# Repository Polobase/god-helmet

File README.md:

# God Helmet: 8-coil weak-field headset (ESP32 + AD5328 + web app over Bluetooth or USB)

A DIY recreation of the Persinger/Koren "God Helmet", the 8-coil Shakti and the circumcerebral "Octopus":
- 8 small coils on a Velcro headband;
- an AD5328 8-channel ±10 V DAC;
- an ESP32 that runs the signals in real time: ESP32-S3, classic ESP32, ESP32-C3 or ESP32-C6, without a display;
- a **web app** (the Nuxt site in [site/](site)) that connects over **Bluetooth LE** or a **USB cable**, and installs the firmware;
- or, without phone or computer, a **2.8" touchscreen board** that runs the programs from its microSD card ([docs/STANDALONE.md](docs/STANDALONE.md)).

It ships **176 programs**, each checked against its source ([docs/PRESET_AUDIT.md](docs/PRESET_AUDIT.md)): Todd Murphy's Shiva and Shakti sessions rebuilt from the vendor's descriptions (with reversed-polarity coils where the Shakti wiring needs them), the Persinger lab's protocols (sensed presence, Thomas pulse, circumcerebral rotations, Swann remote viewing, paired sessions), the timing of clinical low-field methods (LFMS, T-PEMF, Cnp, theta-burst, BHFS), and the independent sham-controlled tests. Each program states the evidence for the original protocol and how closely this helmet can follow it: 14 play published values as published, 133 are rebuilt from descriptions, 16 copy only the timing of a method whose field is out of reach, and 13 are this project's own designs. Whether the first build can host the experiments at all is the subject of [docs/HARDWARE_AUDIT.md](docs/HARDWARE_AUDIT.md). Each program's page also has a **Brain** tab that shows where each program's field goes on a 3D brain, **30 guided sessions** with beat audio and questionnaires, and the means to **test it all honestly**:
- blinded real/sham sessions;
- hash-committed, blind-judged remote-viewing and telepathy trials with exact statistics.

> **Read [docs/SAFETY.md](docs/SAFETY.md) first.** Not for people with epilepsy or seizure history, psychiatric conditions, or implanted electronics. Battery power only. Experimental, non-medical.
>
> **Honest expectations.** The fields are about 1–8 µT at the cortex, about a million times weaker than TMS, and the induced electric field is microvolts to millivolts per metre. The best double-blind test (Granqvist 2005, N = 89) found no effect of the field; suggestibility predicted the experiences. See [docs/RESEARCH.md](docs/RESEARCH.md).

## How it fits together

```
 phone / laptop browser                     control box                                  headband
 ┌──────────────────────┐ Bluetooth / USB┌──────────────┐  SPI + LDAC  ┌──────────┐ 2.2 kΩ ×8  ┌─────────┐
 │ web app (site/):     │◄──────────────►│  ESP32       │─────────────►│ AD5328   │──────────► │ 8 coils │
 │ programs,            │  JSON-RPC +    │  2 kHz engine│              │ ±10 V ×8 │◄─ returns ─│         │
 │ placement, trials    │  live status   │  log, trials │  PhotoMOS ◄──┤          │  PhotoMOS  └─────────┘
 └──────────────────────┘                └──────────────┘  STOP button └──────────┘
```

- **The app** (tabs: Programs, Guides, Trials, Log, Helmet, Docs) holds:
  - the program library, searchable, browsed by category, by placement (all 47 placements in use), by scalp site (a site explorer for every 10-10 site) or by the experience a program aims at;
  - a page for each program with tabs:
    - **Overview:** phases, waveforms and an in-browser preview of the coil activity;
    - **Placement:** the coils on a head map from above and from both sides, and a coil-by-coil checklist with tape-measure directions in centimetres for your head;
    - **Brain:** estimated field per brain region (cored-coil model on the Brainnetome and CerebrA atlases), what electrode or TMS stimulation of each region produced, and the claims made for it;
    - **Sources:** the evidence level and the sources;
  - a Start panel on each program page that lists what is ready (connection, safety page, head measured, coils placed, calibration, time since the last session);
  - guided sessions (Gateway-style, remote viewing, ESP training, sleep) with binaural, monaural or isochronic audio, a blinded helmet arm and questionnaires;
  - blinded remote-viewing and telepathy trials with their picture pool (Trials), and calibration, the wiring check, settings and firmware install (Helmet);
  - all documentation (the Docs tab renders `docs/*.md` and a reference of every program).

  It has a **demo mode** that runs the same engine in the browser, so everything can be explored without hardware.
- **The helmet** holds:
  - the real-time engine, with all 8 coils updated together at 2 kHz;
  - the hidden blind choices (real/sham, RV target, with SHA-256 commitments);
  - the session and trial log;
  - the safety interlocks: STOP button, arming switch, field ceiling, 60-min cap.

  A running session continues if the phone or computer disconnects, and the app shows it again when it reconnects. If the helmet itself restarts, the session's log entry says why and how long it ran.

## What's here

| Path | Contents |
|---|---|
| [docs/RESEARCH.md](docs/RESEARCH.md) | The evidence review: Persinger lab, independent tests, Murphy's claims, mainstream low-field science, psi evidence, **states → brain regions → helmet protocols**, lecture notes |
| [docs/HISTORY.md](docs/HISTORY.md) | Military, intelligence and health-agency history: ELF research, remote-viewing programmes, Gateway, the replication controversy, WHO/IARC/ICNIRP |
| [docs/EFFECT_SENSED_PRESENCE.md](docs/EFFECT_SENSED_PRESENCE.md), [docs/EFFECT_OUT_OF_BODY.md](docs/EFFECT_OUT_OF_BODY.md), [docs/EFFECT_REMOTE_VIEWING.md](docs/EFFECT_REMOTE_VIEWING.md) | Articles on the three most reported effects: what people report, the lab record and independent tests, the science without a helmet, checked YouTube videos, reading lists and how to test each with this helmet |
| [docs/SIGNALS.md](docs/SIGNALS.md) | What the coils play: coil physics and ICNIRP compliance, the Persinger-lab signals rebuilt from primary sources, Murphy's signal families, clinical timings |
| [docs/PRESET_FORMAT.md](docs/PRESET_FORMAT.md) | The program file format, every signal and coil mode, the pulse-table generators, the preset checker |
| [docs/PRESET_AUDIT.md](docs/PRESET_AUDIT.md) | Every program against its source: flaw, decision, deciding page |
| [docs/HARDWARE_AUDIT.md](docs/HARDWARE_AUDIT.md) | Can the first build host the experiments? Verdict per family, ledger, bench protocol |
| [docs/HARDWARE_REQUIREMENTS.md](docs/HARDWARE_REQUIREMENTS.md) | The changes the audit forces, with numbers and cost |
| [docs/AUDIT_SUMMARY.md](docs/AUDIT_SUMMARY.md) | The audit on one page |
| docs/LIBRARY_*.md | Reading notes from the library, one page per family of sources: what each paper or vendor page states, with page and passage |
| [docs/BRAIN_VIEW.md](docs/BRAIN_VIEW.md) | How the brain view's field map is computed, its accuracy, data and licences |
| [docs/GUIDES.md](docs/GUIDES.md), [docs/QUESTIONNAIRES.md](docs/QUESTIONNAIRES.md) | Guided-session format, audio engine, questionnaires and scoring |
| [docs/WIRING.md](docs/WIRING.md) | Schematic, coil leads (inner = signal, outer = return), pin tables (S3, classic ESP32, C3, C6, 2.8" display board), arming switch, Cat6A pair mapping |
| [docs/STANDALONE.md](docs/STANDALONE.md) | The 2.8" touchscreen board without the app: flashing, the SD-card program pack, clock, screens |
| [docs/PLACEMENT.md](docs/PLACEMENT.md) | The 10-10 system, finding sites with a tape measure, the standard and program-specific layouts, depth and field per target |
| [docs/CALIBRATION.md](docs/CALIBRATION.md) | Bench test of the module, wiring checks, µT/mA calibration with a phone |
| [docs/EXPERIMENTS.md](docs/EXPERIMENTS.md) | Blinded sessions, remote-viewing and telepathy protocols, statistics |
| [docs/BLE_PROTOCOL.md](docs/BLE_PROTOCOL.md) | GATT service, framing, the USB line protocol, operations, session JSON, trial commitment |
| [docs/SAFETY.md](docs/SAFETY.md) | Contraindications, rules, built-in safeguards |
| [presets/](presets) | The 176 programs (JSON), shared by the app and the firmware tests. `presets/archive/` holds the 28 that were taken out |
| [guides/](guides) | The 30 guided sessions (JSON) |
| [firmware/](firmware) | PlatformIO project: engine, Bluetooth and USB transports, experiments, log |
| [site/](site) | The Nuxt site: landing page, articles, docs and the control app. `site/core/` holds the engine, protocol and library code that is tested against the firmware. Cloudflare Pages builds it; `.github/workflows/pages.yml` publishes the firmware images for its installer |
| [hardware/](hardware) | Bill of materials, coil clip (OpenSCAD), schematic generator |
| [tools/](tools) | Python: coil field estimate, point tables, WAV → table, calibration fit, trial statistics; Node: brain-view asset builder |

## Quick start

### Supported boards

| Board | Chip | Bluetooth | USB | Display | Firmware env |
|---|---|---|---|---|---|
| ESP32-S3-DevKitC-1 (N8R8 / N16R8, 8 MB flash) | ESP32-S3 | yes | yes | – | `esp32s3` |
| ESP32 DevKitC (WROOM-32, 4 MB) | ESP32 | yes | yes | – | `esp32dev` |
| ESP32-C3-DevKitM-1, C3 Super Mini (4 MB) | ESP32-C3 | yes | yes | – | `esp32c3` |
| ESP32-C6-DevKitC-1 and other C6 boards (4 MB or more) | ESP32-C6 | yes | yes | – | `esp32c6` |
| 2.8" ESP32-32E display board | ESP32 | optional | yes | touchscreen | `esp32e_lcd28` |

Pins for each board: [docs/WIRING.md](docs/WIRING.md).

**Install from the app** (no other software): Helmet → **Install the firmware**, in Chrome or Edge on a computer, with the board on USB. It recognises the chip and asks before erasing.

**Firmware** ([PlatformIO](https://platformio.org/)):

```sh
cd firmware
./test/run_host_tests.sh      # engine, JSON, BLE framing, every preset rendered at 2 kHz
pio run -e esp32s3 -t upload  # ESP32-S3-DevKitC-1 (-e esp32dev, -e esp32c3, -e esp32c6; -e esp32e_lcd28: 2.8" display board)
pio device monitor            # prints the Bluetooth name, e.g. GodHelmet-3F2A
scripts/web_bundle.sh ../site/public/firmware     # images + manifests for the app's installer (CI does this)
```

Standalone touchscreen board: `pio run -e esp32e_lcd28 -t upload`, then `npm run sd-pack -- <dir>` in `site/` for the SD card ([docs/STANDALONE.md](docs/STANDALONE.md)).

**App:**

```sh
cd site
npm install
npm test                      # JS engine matches the C++ engine; field model; guides; protocol and trial logic; every program file
npm run check-presets         # validate every program file (also one file: node scripts/check-preset.mjs ../presets/<id>.json)
npm run table -- list         # exact pulse tables (theta-burst, Thomas, LFMS, ...)
npm run dev                   # http://localhost:3000 (Web Bluetooth and Web Serial work on localhost)
```

**Deploy:** Cloudflare Pages builds `site/` on every push ([site/README.md](site/README.md)). The firmware images for the installer are built by `.github/workflows/pages.yml` and served from GitHub Pages (Settings → Pages → Source: **GitHub Actions**).

**First use:**
1. Open the app in Chrome/Edge (iPhone: Bluefy) and press **Bluetooth**, or plug the helmet into the computer and press **USB**.
2. Read and accept **Safety**.
3. Do the bench test and calibration (docs/CALIBRATION.md) before wearing the helmet.

## Status

- **Verified here:**
  - all five firmware targets build;
  - host unit tests pass;
  - the JavaScript engine reproduces the C++ engine's output for every preset (whole sessions plus a 3.5 ms-resolution window);
  - protocol, blind reveal and trial commitment logic are tested against the demo helmet;
  - the app builds and runs in a headless browser in demo mode.
- **Not yet verified on hardware:**
  - BLE with a real phone;
  - the module's transfer function;
  - SPI/LDAC timing;
  - the coils' real µT/mA.

  docs/CALIBRATION.md walks through them.

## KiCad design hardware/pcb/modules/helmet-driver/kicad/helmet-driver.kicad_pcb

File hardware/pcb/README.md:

# hardware/pcb: the helmet driver board as code

This folder holds the god-helmet's controller board, **helmet-driver** (`modules/helmet-driver/`: an ESP32-S3,
eight current-output coil drivers and two isolated tES outputs, fed from USB-C), and the toolchain that turns it
into order files for JLCPCB:

```
spec.md + module.yaml ─► schematic.ts ─► bun run sch ─► PDF review ─► sch:approve ─► bun run pcb ─► bun run fab ─► bun run order
                         (KiCad 10, ERC 0/0,           (you)         (sha256 in     (placed,        (Gerbers, BOM,   (ORDER.md and
                          netlist round-trip)                          module.yaml)   routed, DRC)    CPL, README)     upload files)
            ngspice benches (bun run sim) check the critical circuits along the way
```

The schematic is written as TypeScript (`modules/<id>/schematic.ts`) and generated into a native KiCad 10
schematic, one sheet or a root sheet with pages (`sheets`, [docs/schematic-as-code.md](docs/schematic-as-code.md)
§3a); parts come from `parts/*.yaml`, with their KiCad symbols and footprints vendored in `lib/kicad/`. The
toolchain builds standalone PCBs of this kind: one board per `modules/<id>/`, 2 or 4 copper layers, assembled by
JLCPCB.

## Prerequisites

- **Bun ≥ 1.4.2** (`bun install` once, for zod, yaml and fflate)
- **KiCad 10.0.x** (tested with 10.0.6): `kicad-cli` and KiCad's bundled Python with `pcbnew`
- **ngspice** (47 or newer) for `bun run sim`
- **Java ≥ 25** for the Freerouting autorouter (Homebrew's keg-only OpenJDK is found without PATH). Freerouting
  2.4.1 itself is fetched into `.tools/` on first use, sha256-pinned.
- TI SPICE models: `bun run models:fetch` downloads them into the gitignored `models/` (TI's terms: never committed).

`bun run doctor` checks all of these and prints install hints; it never installs anything. Details and known
KiCad issues: [docs/environment.md](docs/environment.md).

## Commands

Run from `hardware/pcb/`. `<id>` is a folder name in `modules/` (`helmet-driver`).

| Command | What it does |
|---|---|
| `bun run doctor` | report tools, versions and paths |
| `bun run validate [-- <id>]` | check `module.yaml` and every `parts/*.yaml` (and their symbols and footprints in `lib/kicad`) |
| `bun run lib:import` | vendor the KiCad stock symbols and footprints that `parts/*.yaml` uses into `lib/kicad/` (reads the local KiCad install) |
| `bun run sim -- modules/<id>/sim/<bench>.cir` | run an ngspice bench and check its `* @assert` lines |
| `bun run models:fetch` | download the vendor SPICE models |
| `bun run sch -- <id>` | generate the schematic, ERC 0/0, netlist round-trip, PDF (one page per sheet) and `build/<id>/review.md` |
| `bun run sch:check` | regenerate every schematic in memory and fail on any difference to the committed files (every page file of a schematic with pages, and no leftover page file) |
| `bun run sch:approve -- <id> --yes` | record your approval of the reviewed PDF in `module.yaml` (only after your OK) |
| `bun run pcb -- <id>` | place and route the board from its approved schematic and `modules/<id>/pcb.ts`, DRC with parity |
| `bun run render -- <id>` | 3D renders of the assembled board |
| `bun run fab -- <id> [--draft]` | JLCPCB files in `build/<id>/fab/`: Gerbers, drill, BOM, CPL, README checklist |
| `bun run order -- <id>` | collect one cart's upload files and `ORDER.md` in `build/<id>/order/` |
| `bun run verify:outputs -- <id>` | regenerate fab and order in a temp folder and compare them with `build/<id>/` |
| `bun run typecheck` | TypeScript, no emit |
| `bun run test` / `test:unit` / `test:full` | all tests (KiCad and ngspice suites skip when the tool is missing) / unit tests only / missing tools fail |
| `bun run check:fast` | typecheck, unit tests, validate and sch:check |
| `bun run check` | the same with the KiCad and ngspice tests |

Generated output goes to `build/` (gitignored). KiCad owns `modules/<id>/kicad/<id>.kicad_pcb` once it exists; the
`.kicad_sch` files (the root and, for a schematic with pages, `<id>-<page>.kicad_sch`) are generated and never saved
from KiCad.

## The gated workflow

1. **Specify:** `spec.md` (requirements, sources), `module.yaml` (board options, current draw per supply rail,
   JLCPCB options), `design-notes.md`; ngspice benches in `sim/` for the risky circuits.
2. **Schematic:** `schematic.ts` → `bun run sch`. Every gate must pass: ERC with 0 errors and 0 warnings and no
   exclusions, and KiCad's netlist equal to the design.
3. **Review:** you read the schematic PDF (`build/<id>/<id>-schematic.pdf`) and `review.md`. Changes go back into
   `schematic.ts`.
4. **Approve:** only after your explicit OK, `bun run sch:approve -- <id> --yes` stores the schematic's sha256.
   Layout and fab refuse an unapproved or changed schematic.
5. **Layout:** `bun run pcb`, or by hand in KiCad; DRC with schematic parity must report 0/0.
6. **Fab and order files:** `bun run fab`, then `bun run order`. fab refuses unverified part sourcing, DRC
   findings and stale inputs.
7. **Order:** you upload the files on jlcpcb.com, check JLCPCB's Gerber viewer and placement preview, and order.
   **The tools never upload anything and never place an order.**

Step by step: [docs/workflow.md](docs/workflow.md). Layout: [docs/pcb.md](docs/pcb.md). JLCPCB's file formats,
rules and open questions: [docs/jlcpcb.md](docs/jlcpcb.md). Why schematics are code:
[docs/schematic-as-code.md](docs/schematic-as-code.md).

## Folder layout

| Path | Contents |
|---|---|
| `modules/helmet-driver/` | the board: `module.yaml`, `spec.md`, `design-notes.md`, `schematic.ts`, `sim/`, later `kicad/` and `pcb.ts` |
| `parts/` | one YAML file per part family: KiCad symbol and footprint, assembly method, sourcing per value (MPN, LCSC number, verified source and date) |
| `lib/kicad/` | vendored KiCad 10.0.6 stock symbols and footprints (`GHP_*` libraries), `SOURCES.json` provenance, `LICENSE.md` |
| `tools/` | the toolchain (TypeScript on Bun; `tools/pcb/kicad_pcb.py` runs in KiCad's Python) |
| `tests/` | integration tests and fixtures, including the generic pipeline-proof schematic and the pages-proof schematic (three pages) |
| `docs/` | reference and decision records |

## Licences and notices

- `lib/kicad/` holds copies of the KiCad libraries, licensed CC-BY-SA-4.0 with the KiCad library exception
  (`lib/kicad/LICENSE.md`).
- `tools/fab/transformations.csv` is the Fabrication Toolkit's rotation table, Apache-2.0
  (`tools/fab/LICENSE-Apache-2.0.txt`, `tools/fab/NOTICE.md`).

## Origin

The toolchain comes from the author's own earlier hardware project, a separate private repository, and was trimmed
to standalone boards for god-helmet on 2026-11-13.

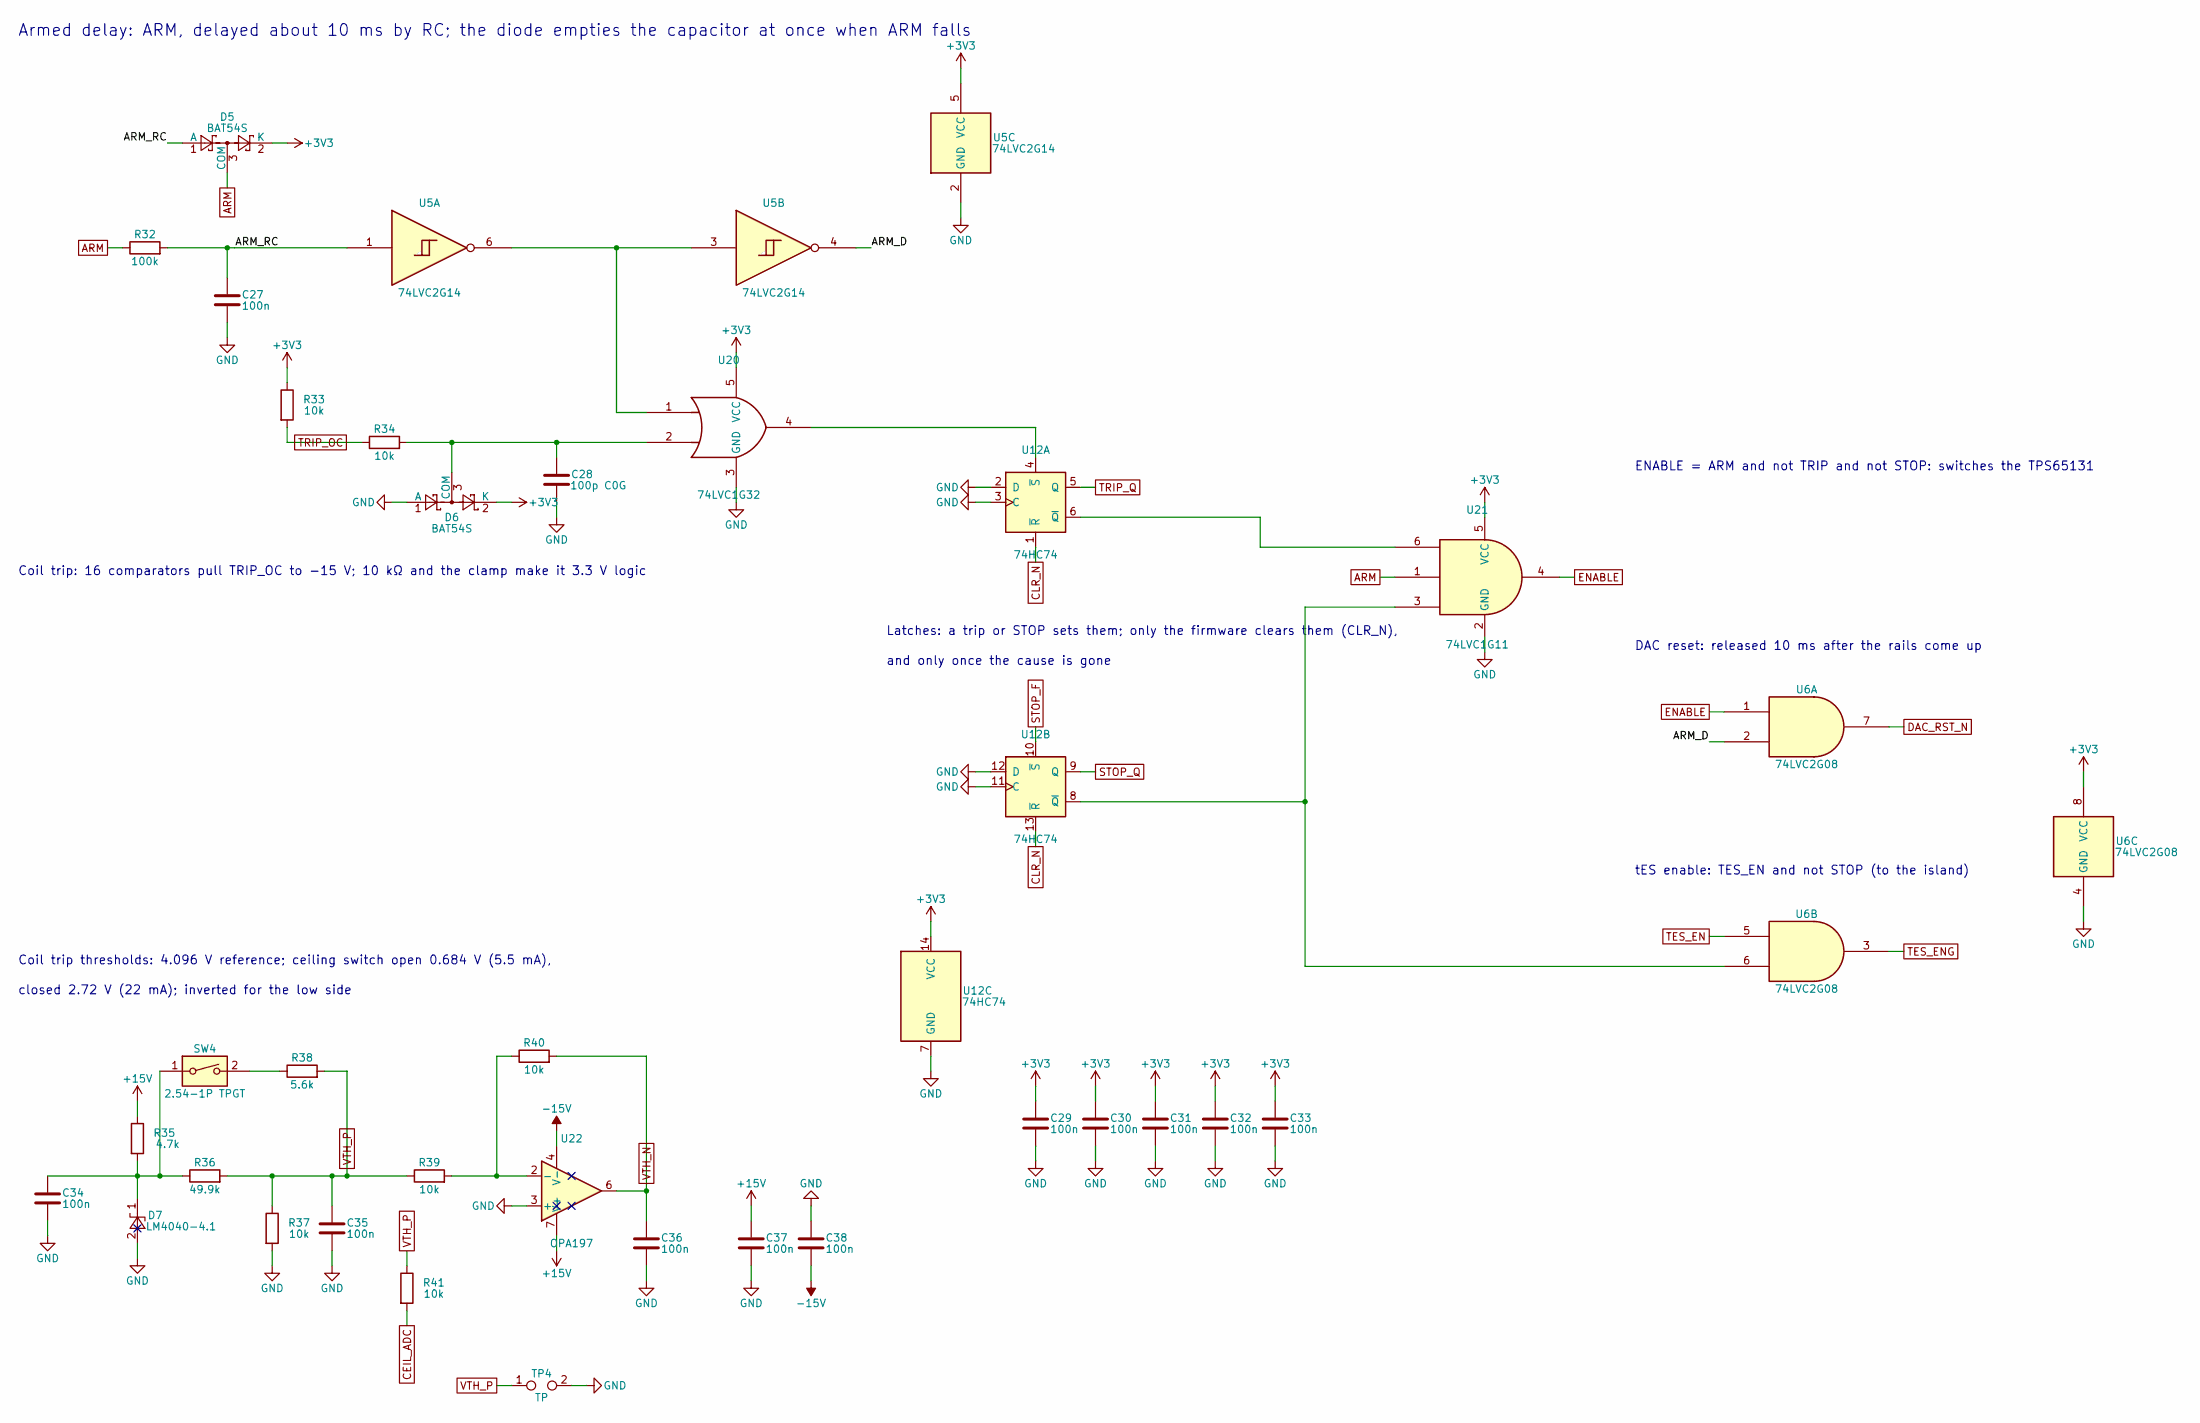
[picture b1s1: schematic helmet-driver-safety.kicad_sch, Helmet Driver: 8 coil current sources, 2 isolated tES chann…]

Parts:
C27, C29, C30, C31, C32, C33, C34, C35, C36, C37, C38: 100n; C_0603_1608Metric; MPN CC0603KRX7R9BB104; LCSC C14663
C28: 100p C0G; C_0603_1608Metric; MPN CL10C101JB8NNNC; LCSC C14858
D5, D6: BAT54S; SOT-23; MPN BAT54S,215; LCSC C47546
D7: LM4040-4.1; SOT-23; MPN LM4040AIM3-4.1/NOPB; LCSC C126807
R32: 100k; R_0603_1608Metric; MPN 0603WAF1003T5E; LCSC C25803
R33, R34, R41: 10k; R_0603_1608Metric; MPN 0603WAF1002T5E; LCSC C25804
R35: 4.7k; R_0603_1608Metric; MPN 0603WAF4701T5E; LCSC C23162
R36: 49.9k; R_0603_1608Metric; MPN RT0603BRD0749K9L; LCSC C705780
R37, R39, R40: 10k; R_0603_1608Metric; MPN RT0603BRD0710KL; LCSC C95204
R38: 5.6k; R_0603_1608Metric; MPN 0603WAF5601T5E; LCSC C23189
SW4: 2.54-1P TPGT; SW_DIP_SPSTx01_Slide_6.7x4.1mm_W8.61mm_P2.54mm_LowProfile; MPN 2.54-1P TPGT; LCSC C7421519
TP4: TP; TestPoint_2Pads_Pitch2.54mm_Drill0.8mm; PartKey testpoint-2pad
U5: 74LVC2G14; SOT-23-6; MPN SN74LVC2G14DBVR; LCSC C12401
U6: 74LVC2G08; SSOP-8_2.95x2.8mm_P0.65mm; MPN SN74LVC2G08DCTR; LCSC C352973
U12: 74HC74; SOIC-14_3.9x8.7mm_P1.27mm; MPN SN74HC74DR; LCSC C6762
U20: 74LVC1G32; SOT-23-5; MPN SN74LVC1G32DBVR; LCSC C10096
U21: 74LVC1G11; SOT-23-6; MPN SN74LVC1G11DBVR; LCSC C22046
U22: OPA197; SOIC-8_3.9x4.9mm_P1.27mm; MPN OPA197IDR; LCSC C79274

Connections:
+3V3: C29.1, C30.1, C31.1, C32.1, C33.1, D5.2 (K), D6.2 (K), R33.1, U5.5 (VCC), U6.8 (VCC), U12.14 (VCC), U20.5 (VCC), U21.5 (VCC); also elsewhere on the board
+15V: C37.1, R35.1, U22.7 (V+); also elsewhere on the board
-15V: C38.2, U22.4 (V-); also elsewhere on the board
/Safety logic: TRIP and STOP latches, ENABLE, coil trip thresholds/ARM_D: U5.4, U6.2
/Safety logic: TRIP and STOP latches, ENABLE, coil trip thresholds/ARM_RC: C27.1, D5.1 (A), R32.2, U5.1
ARM: D5.3 (COM), R32.1, U21.1; also elsewhere on the board
CEIL_ADC: R41.2; also elsewhere on the board
CLR_N: U12.1 (~R), U12.13 (~R); also elsewhere on the board
DAC_RST_N: U6.7; also elsewhere on the board
ENABLE: U6.1, U21.4; also elsewhere on the board
GND: C27.2, C28.2, C29.2, C30.2, C31.2, C32.2, C33.2, C34.2, C35.2, C36.2, C37.2, C38.1, D6.1 (A), D7.2 (A), R37.2, TP4.2, U5.2 (GND), U6.4 (GND), U12.2 (D), U12.3 (C), U12.7 (GND), U12.11 (C), U12.12 (D), U20.3 (GND), U21.2 (GND), U22.3 (+); also elsewhere on the board
unnamed: C28.1, D6.3 (COM), R34.2, U20.2
unnamed: C34.1, D7.1 (K), R35.2, R36.1, SW4.1
unnamed: R38.1, SW4.2
unnamed: U12.6 (~Q), U21.6
unnamed: U12.4 (~S), U20.4
unnamed: U6.6, U12.8 (~Q), U21.3
unnamed: U5.3, U5.6, U20.1
unnamed: R39.2, R40.1, U22.2 (-)
STOP_F: U12.10 (~S); also elsewhere on the board
STOP_Q: U12.9 (Q); also elsewhere on the board
TES_EN: U6.5; also elsewhere on the board
TES_ENG: U6.3; also elsewhere on the board
TRIP_OC: R33.2, R34.1; also elsewhere on the board
TRIP_Q: U12.5 (Q); also elsewhere on the board
VTH_N: C36.1, R40.2, U22.6; also elsewhere on the board
VTH_P: C35.1, R36.2, R37.1, R38.2, R39.1, R41.1, TP4.1; also elsewhere on the board

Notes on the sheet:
Coil trip thresholds: 4.096 V reference; ceiling switch open 0.684 V (5.5 mA),
and only once the cause is gone
Coil trip: 16 comparators pull TRIP_OC to -15 V; 10 kΩ and the clamp make it 3.3 V logic
ENABLE = ARM and not TRIP and not STOP: switches the TPS65131
closed 2.72 V (22 mA); inverted for the low side
Armed delay: ARM, delayed about 10 ms by RC; the diode empties the capacitor at once when ARM falls
DAC reset: released 10 ms after the rails come up
Latches: a trip or STOP sets them; only the firmware clears them (CLR_N),
tES enable: TES_EN and not STOP (to the island)

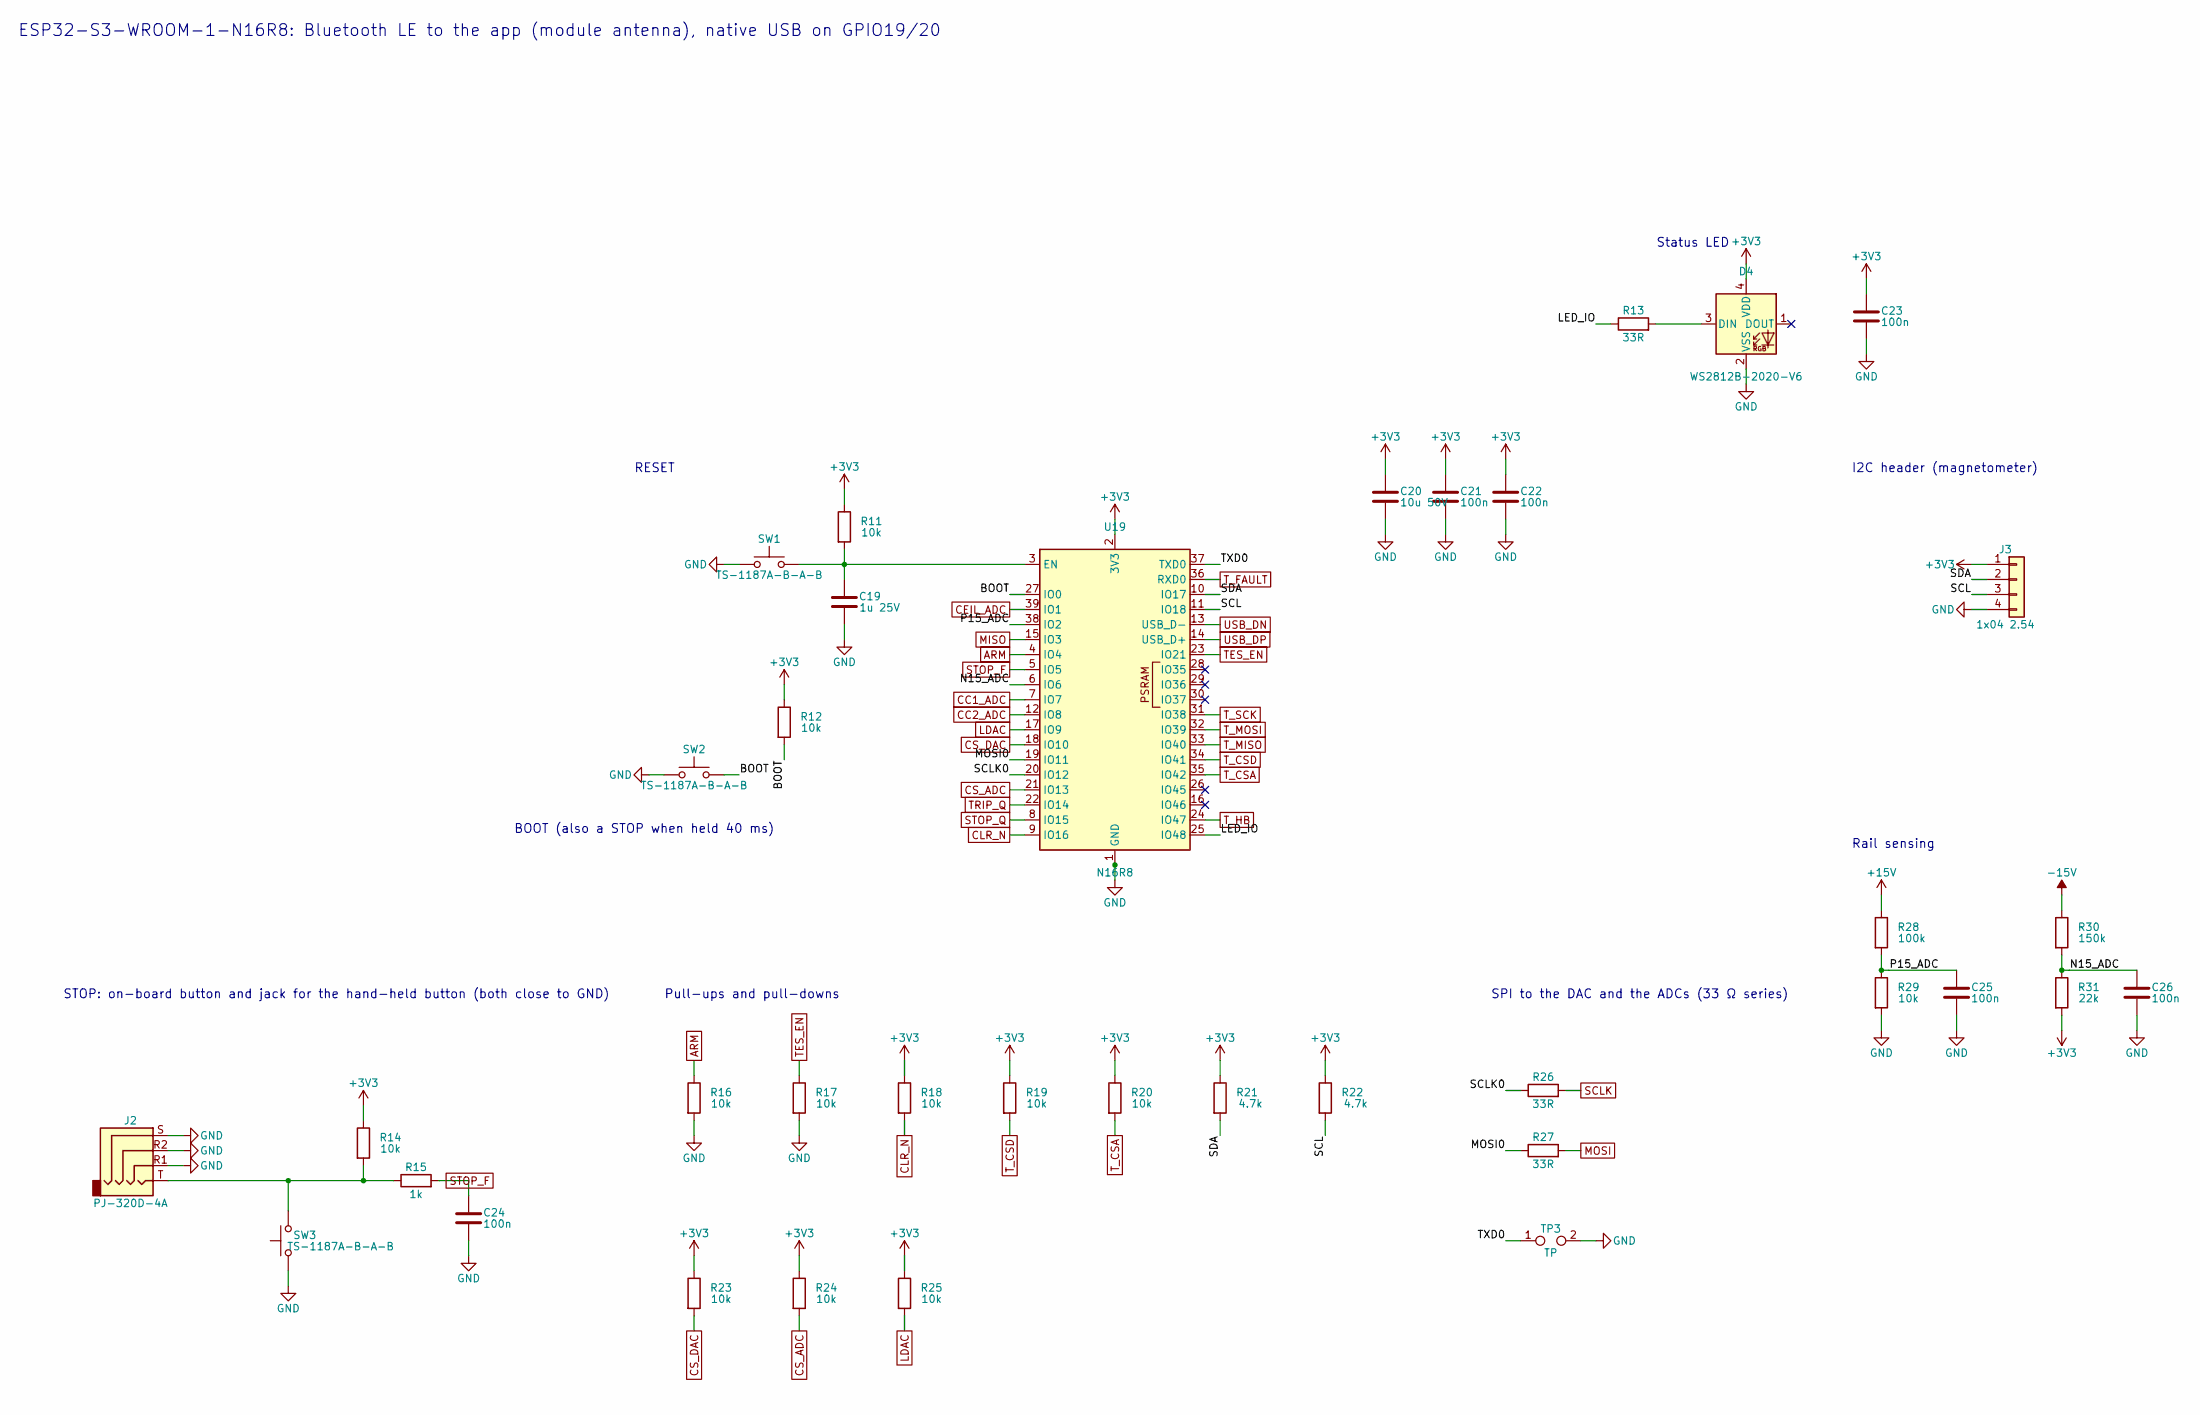
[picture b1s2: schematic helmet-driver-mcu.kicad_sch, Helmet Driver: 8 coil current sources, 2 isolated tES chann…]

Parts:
C19: 1u 25V; C_0603_1608Metric; MPN CL10B105KA8NNNC; LCSC C29936
C20: 10u 50V; C_1206_3216Metric; MPN CL31A106KBHNNNE; LCSC C13585
C21, C22, C23, C24, C25, C26: 100n; C_0603_1608Metric; MPN CC0603KRX7R9BB104; LCSC C14663
D4: WS2812B-2020-V6; LED_WS2812B-2020_PLCC4_2.0x2.0mm; MPN WS2812B-2020-V6; LCSC C52917434
J2: PJ-320D-4A; Jack_3.5mm_KoreanHropartsElec_PJ-320D-4A_Horizontal; MPN PJ-320D-4A; LCSC C95562
J3: 1x04 2.54; PinHeader_1x04_P2.54mm_Vertical; MPN PZ254V-11-04P; LCSC C2691448
R11, R12, R14, R16, R17, R18, R19, R20, R23, R24, R25, R29: 10k; R_0603_1608Metric; MPN 0603WAF1002T5E; LCSC C25804
R13, R26, R27: 33R; R_0603_1608Metric; MPN 0603WAF330JT5E; LCSC C23140
R15: 1k; R_0603_1608Metric; MPN 0603WAF1001T5E; LCSC C21190
R21, R22: 4.7k; R_0603_1608Metric; MPN 0603WAF4701T5E; LCSC C23162
R28: 100k; R_0603_1608Metric; MPN 0603WAF1003T5E; LCSC C25803
R30: 150k; R_0603_1608Metric; MPN 0603WAF1503T5E; LCSC C22807
R31: 22k; R_0603_1608Metric; MPN 0603WAF2202T5E; LCSC C31850
SW1, SW2, SW3: TS-1187A-B-A-B; SW_Push_1P1T_XKB_TS-1187A; MPN TS-1187A-B-A-B; LCSC C318884
TP3: TP; TestPoint_2Pads_Pitch2.54mm_Drill0.8mm; PartKey testpoint-2pad
U19: N16R8; ESP32-S3-WROOM-1; MPN ESP32-S3-WROOM-1-N16R8; LCSC C2913202

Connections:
+3V3: C20.1, C21.1, C22.1, C23.1, D4.4 (VDD), J3.1, R11.1, R12.1, R14.1, R18.1, R19.1, R20.1, R21.1, R22.1, R23.1, R24.1, R25.1, R31.2, U19.2 (3V3); also elsewhere on the board
+15V: R28.1; also elsewhere on the board
-15V: R30.1; also elsewhere on the board
/ESP32-S3 with Bluetooth LE, buttons, STOP, status LED, sensing/BOOT: R12.2, SW2.2, U19.27 (IO0)
/ESP32-S3 with Bluetooth LE, buttons, STOP, status LED, sensing/LED_IO: R13.1, U19.25 (IO48)
/ESP32-S3 with Bluetooth LE, buttons, STOP, status LED, sensing/MOSI0: R27.1, U19.19 (IO11)
/ESP32-S3 with Bluetooth LE, buttons, STOP, status LED, sensing/N15_ADC: C26.1, R30.2, R31.1, U19.6 (IO6)
/ESP32-S3 with Bluetooth LE, buttons, STOP, status LED, sensing/P15_ADC: C25.1, R28.2, R29.1, U19.38 (IO2)
/ESP32-S3 with Bluetooth LE, buttons, STOP, status LED, sensing/SCL: J3.3, R22.2, U19.11 (IO18)
/ESP32-S3 with Bluetooth LE, buttons, STOP, status LED, sensing/SCLK0: R26.1, U19.20 (IO12)
/ESP32-S3 with Bluetooth LE, buttons, STOP, status LED, sensing/SDA: J3.2, R21.2, U19.10 (IO17)
/ESP32-S3 with Bluetooth LE, buttons, STOP, status LED, sensing/TXD0: TP3.1, U19.37 (TXD0)
ARM: R16.1, U19.4 (IO4); also elsewhere on the board
CC1_ADC: U19.7 (IO7); also elsewhere on the board
CC2_ADC: U19.12 (IO8); also elsewhere on the board
CEIL_ADC: U19.39 (IO1); also elsewhere on the board
CLR_N: R18.2, U19.9 (IO16); also elsewhere on the board
CS_ADC: R24.2, U19.21 (IO13); also elsewhere on the board
CS_DAC: R23.2, U19.18 (IO10); also elsewhere on the board
GND: C19.2, C20.2, C21.2, C22.2, C23.2, C24.2, C25.2, C26.2, D4.2 (VSS), J2.R1, J2.R2, J2.S, J3.4, R16.2, R17.2, R29.2, SW1.1, SW2.1, SW3.1, TP3.2, U19.1 (GND), U19.40 (GND), U19.41 (GND); also elsewhere on the board
LDAC: R25.2, U19.17 (IO9); also elsewhere on the board
MISO: U19.15 (IO3); also elsewhere on the board
MOSI: R27.2; also elsewhere on the board
unnamed: D4.3 (DIN), R13.2
unnamed: J2.T, R14.2, R15.1, SW3.2
unnamed: C19.1, R11.2, SW1.2, U19.3 (EN)
SCLK: R26.2; also elsewhere on the board
STOP_F: C24.1, R15.2, U19.5 (IO5); also elsewhere on the board
STOP_Q: U19.8 (IO15); also elsewhere on the board
TES_EN: R17.1, U19.23 (IO21); also elsewhere on the board
TRIP_Q: U19.22 (IO14); also elsewhere on the board
T_CSA: R20.2, U19.35 (IO42); also elsewhere on the board
T_CSD: R19.2, U19.34 (IO41); also elsewhere on the board
T_FAULT: U19.36 (RXD0); also elsewhere on the board
T_HB: U19.24 (IO47); also elsewhere on the board
T_MISO: U19.33 (IO40); also elsewhere on the board
T_MOSI: U19.32 (IO39); also elsewhere on the board
T_SCK: U19.31 (IO38); also elsewhere on the board
USB_DN: U19.13 (USB_D-); also elsewhere on the board
USB_DP: U19.14 (USB_D+); also elsewhere on the board

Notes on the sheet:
SPI to the DAC and the ADCs (33 Ω series)
Pull-ups and pull-downs
Status LED
I2C header (magnetometer)
Rail sensing
STOP: on-board button and jack for the hand-held button (both close to GND)
BOOT (also a STOP when held 40 ms)
ESP32-S3-WROOM-1-N16R8: Bluetooth LE to the app (module antenna), native USB on GPIO19/20
RESET

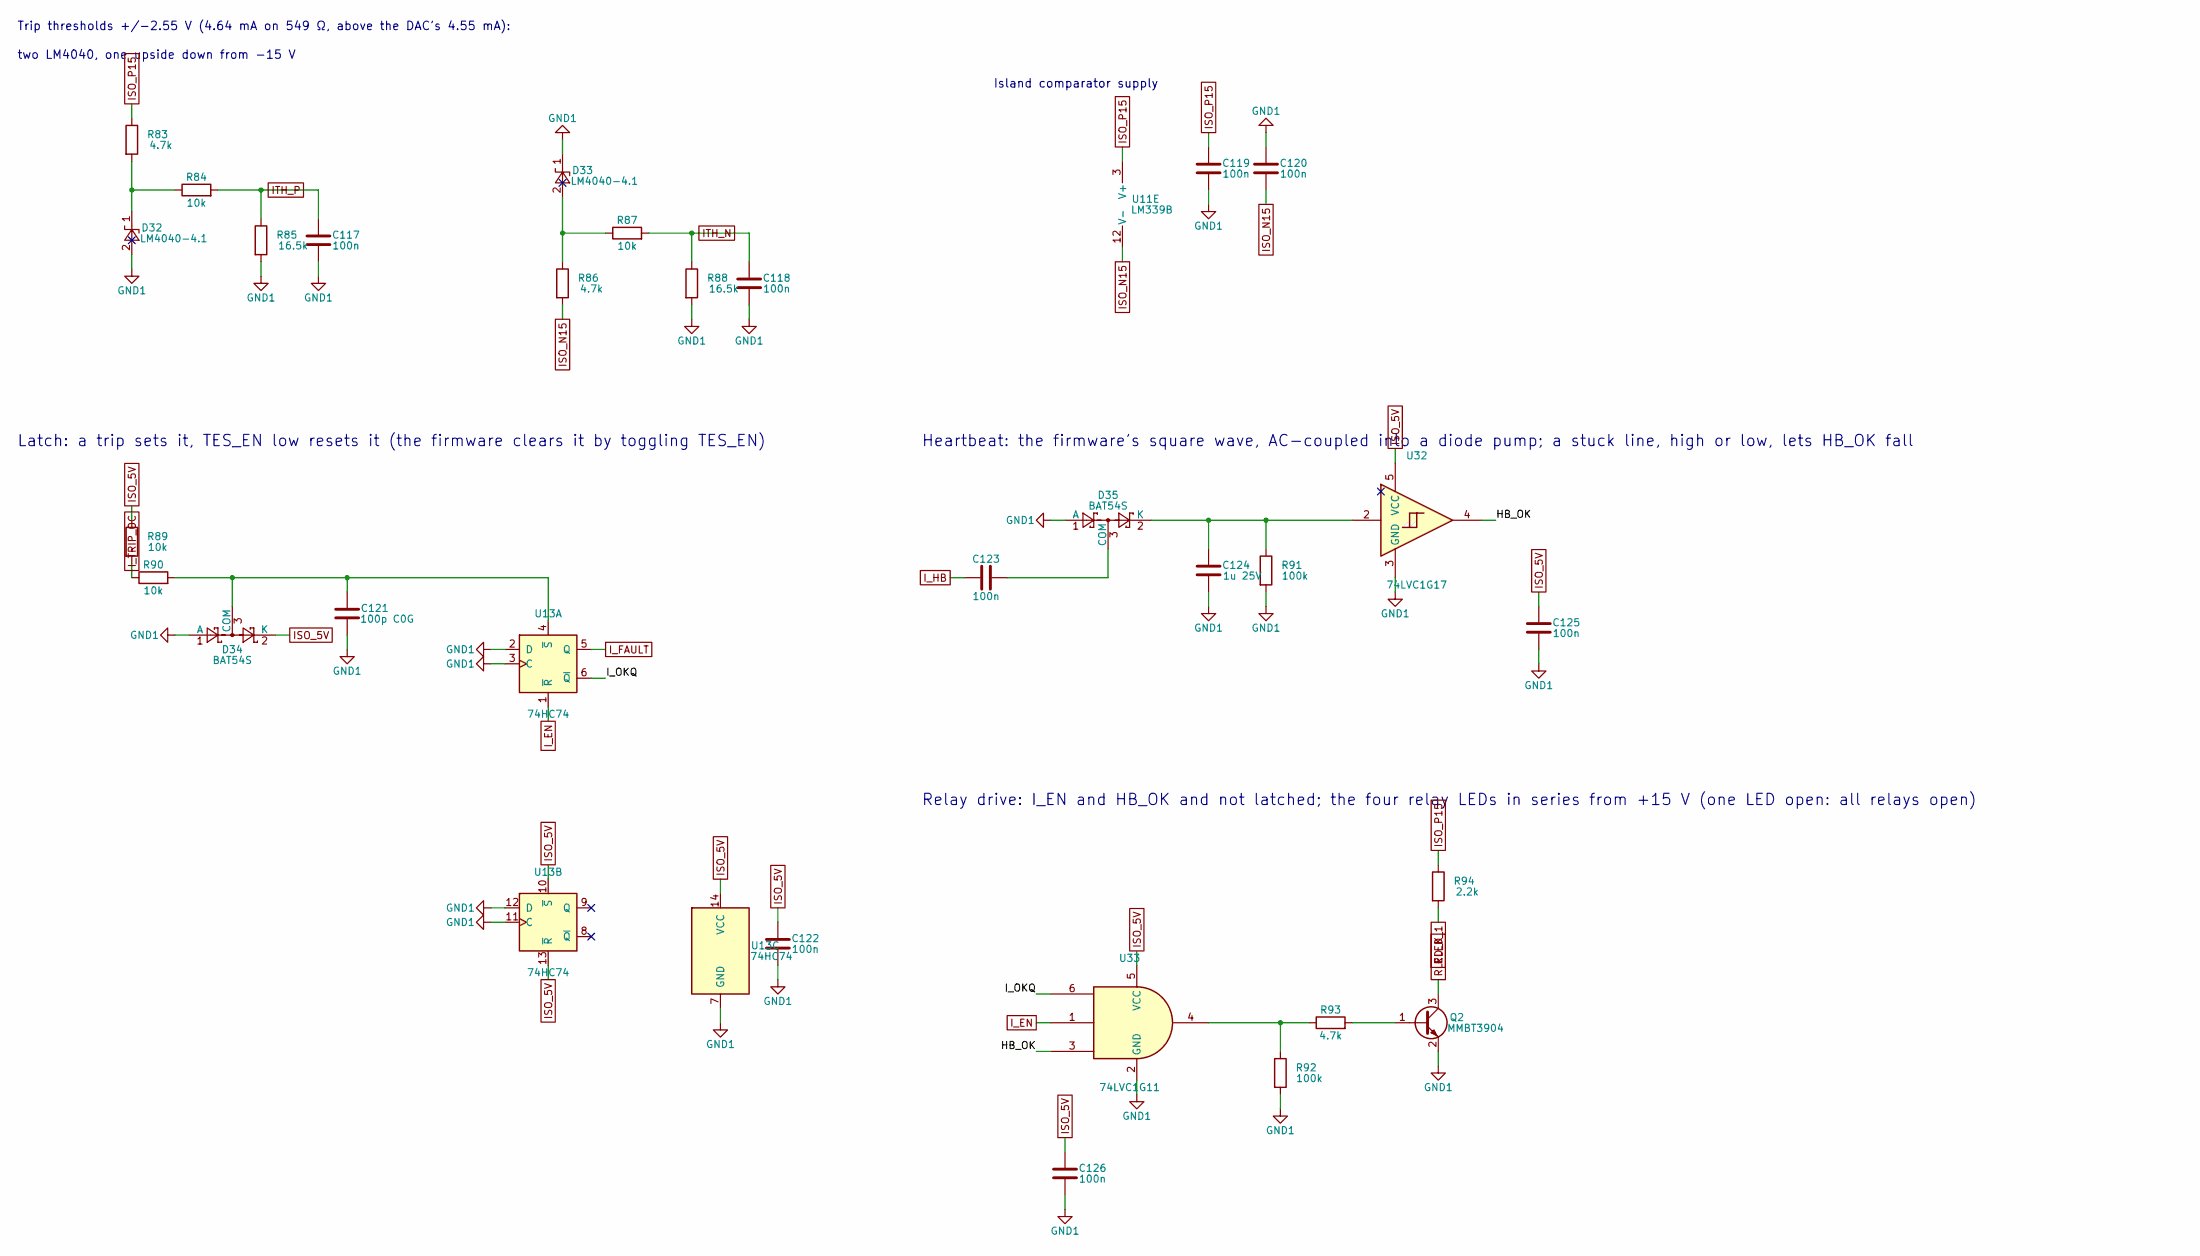
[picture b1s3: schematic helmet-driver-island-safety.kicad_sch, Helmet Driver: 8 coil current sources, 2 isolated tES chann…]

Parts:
C117, C118, C119, C120, C122, C123, C125, C126: 100n; C_0603_1608Metric; MPN CC0603KRX7R9BB104; LCSC C14663
C121: 100p C0G; C_0603_1608Metric; MPN CL10C101JB8NNNC; LCSC C14858
C124: 1u 25V; C_0603_1608Metric; MPN CL10B105KA8NNNC; LCSC C29936
D32, D33: LM4040-4.1; SOT-23; MPN LM4040AIM3-4.1/NOPB; LCSC C126807
D34, D35: BAT54S; SOT-23; MPN BAT54S,215; LCSC C47546
Q2: MMBT3904; SOT-23; MPN MMBT3904(RANGE:100-300); LCSC C20526
R83, R86, R93: 4.7k; R_0603_1608Metric; MPN 0603WAF4701T5E; LCSC C23162
R84, R87, R89, R90: 10k; R_0603_1608Metric; MPN 0603WAF1002T5E; LCSC C25804
R85, R88: 16.5k; R_0603_1608Metric; MPN 0603WAF1652T5E; LCSC C22812
R91, R92: 100k; R_0603_1608Metric; MPN 0603WAF1003T5E; LCSC C25803
R94: 2.2k; R_0603_1608Metric; MPN 0603WAF2201T5E; LCSC C4190
U11: LM339B; SOIC-14_3.9x8.7mm_P1.27mm; MPN LM339BIDR; LCSC C22416291
U13: 74HC74; SOIC-14_3.9x8.7mm_P1.27mm; MPN SN74HC74DR; LCSC C6762
U32: 74LVC1G17; SOT-23-5; MPN SN74LVC1G17DBVR; LCSC C7836
U33: 74LVC1G11; SOT-23-6; MPN SN74LVC1G11DBVR; LCSC C22046

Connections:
/tES island: trip thresholds, latch, heartbeat, relay drive/HB_OK: U32.4, U33.3
/tES island: trip thresholds, latch, heartbeat, relay drive/I_OKQ: U13.6 (~Q), U33.6
GND1: C117.2, C118.2, C119.2, C120.1, C121.2, C122.2, C124.2, C125.2, C126.2, D32.2 (A), D33.1 (K), D34.1 (A), D35.1 (A), Q2.2 (E), R85.2, R88.2, R91.2, R92.2, U13.2 (D), U13.3 (C), U13.7 (GND), U13.11 (C), U13.12 (D), U32.3 (GND), U33.2 (GND); also elsewhere on the board
ISO_5V: C122.1, C125.1, C126.1, D34.2 (K), R89.1, U13.10 (~S), U13.13 (~R), U13.14 (VCC), U32.5 (VCC), U33.5 (VCC); also elsewhere on the board
ISO_N15: C120.2, R86.2, U11.12 (V-); also elsewhere on the board
ISO_P15: C119.1, R83.1, R94.1, U11.3 (V+); also elsewhere on the board
ITH_N: C118.1, R87.2, R88.1; also elsewhere on the board
ITH_P: C117.1, R84.2, R85.1; also elsewhere on the board
I_EN: U13.1 (~R), U33.1; also elsewhere on the board
I_FAULT: U13.5 (Q); also elsewhere on the board
I_HB: C123.1; also elsewhere on the board
I_TRIP_OC: R89.2, R90.1; also elsewhere on the board
unnamed: D32.1 (K), R83.2, R84.1
unnamed: D33.2 (A), R86.1, R87.1
unnamed: C121.1, D34.3 (COM), R90.2, U13.4 (~S)
unnamed: C123.2, D35.3 (COM)
unnamed: C124.1, D35.2 (K), R91.1, U32.2
unnamed: Q2.1 (B), R93.2
unnamed: R92.1, R93.1, U33.4
RLED_1: R94.2; also elsewhere on the board
RLED_K: Q2.3 (C); also elsewhere on the board

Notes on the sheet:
Island comparator supply
Trip thresholds +/-2.55 V (4.64 mA on 549 Ω, above the DAC's 4.55 mA):
Relay drive: I_EN and HB_OK and not latched; the four relay LEDs in series from +15 V (one LED open: all relays open)
two LM4040, one upside down from -15 V
Latch: a trip sets it, TES_EN low resets it (the firmware clears it by toggling TES_EN)
Heartbeat: the firmware's square wave, AC-coupled into a diode pump; a stuck line, high or low, lets HB_OK fall
